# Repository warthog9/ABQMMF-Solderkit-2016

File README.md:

This is the learn to solder badge for the Albuquerque Mini Maker Faire.

License:
	The design is opened based on the Creative Commons CC-BY-SA 4.0
	[https://creativecommons.org/licenses/by-sa/4.0/](https://creativecommons.org/licenses/by-sa/4.0/)

	Copyright on the badge is held by John 'Warthog9' Hawley

	The badges themselves use a silkscreen that has elements that
	have been removed from this repository, they are not required
	for the functionality, and were removed out of respect for the
	various originators of the symbols.

	Rough outline of the balloons was adapted from
	[https://pixabay.com/en/hot-air-balloon-balloon-striped-312574/](https://pixabay.com/en/hot-air-balloon-balloon-striped-312574/)
	which was listed as released into Public Domain when acquired on
	May 27, 2016

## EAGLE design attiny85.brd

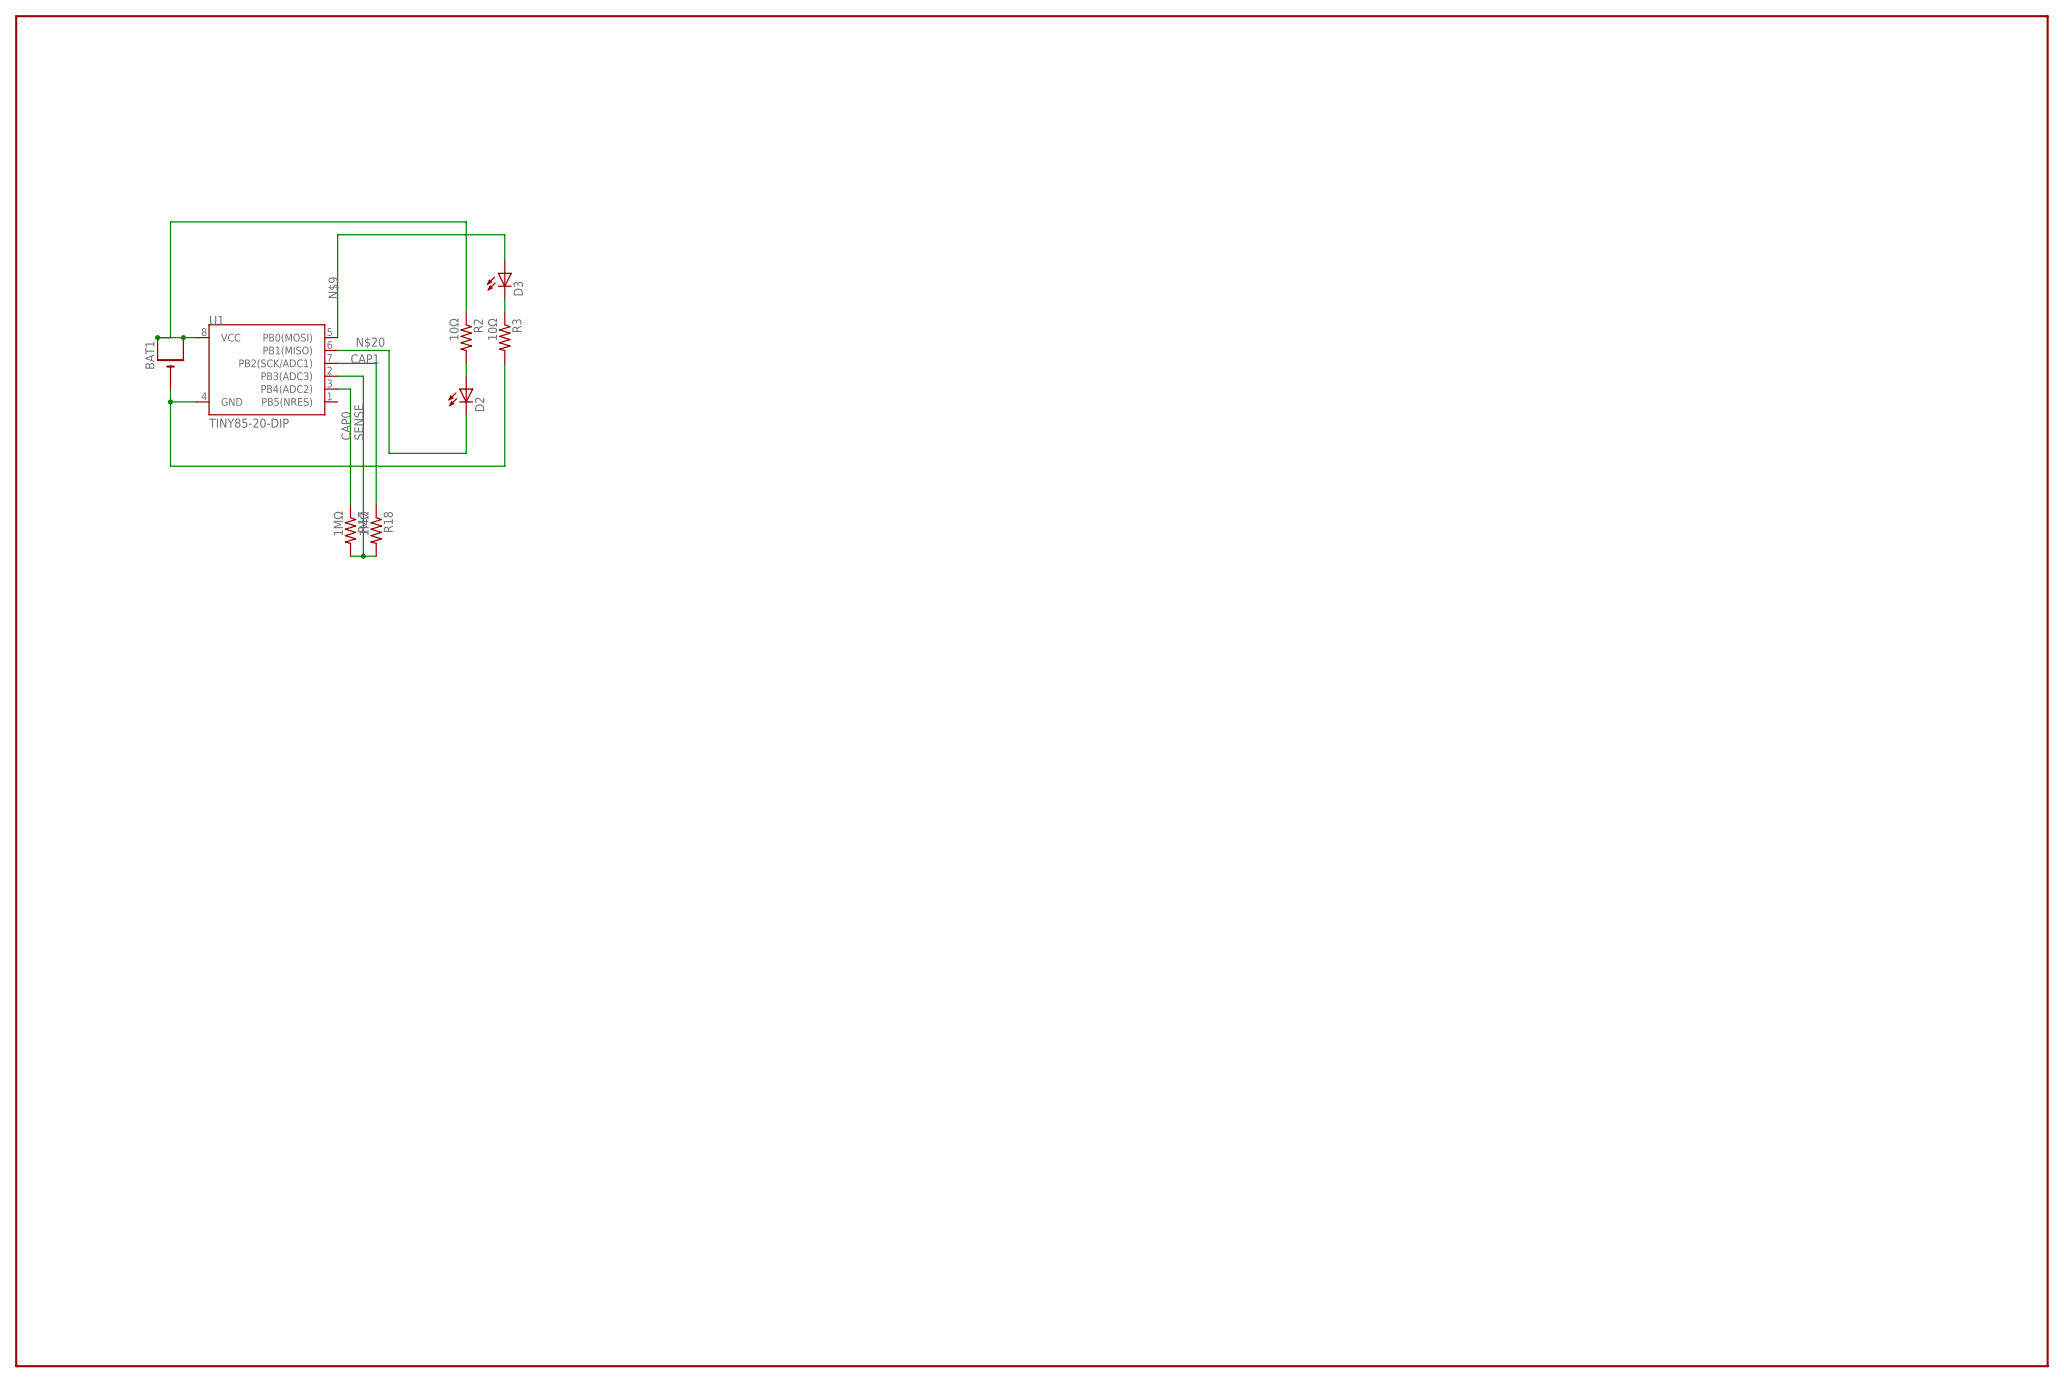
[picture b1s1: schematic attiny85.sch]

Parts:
BAT1: CR2032THM; CR2032-THRU
D2, D3: LED5MM
R2, R3: 10Ω; AXIAL-0.3
R17, R18: 1MΩ; AXIAL-0.3
U1: TINY85-20-DIP; DIP08

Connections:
CAP0: R17.P$1 (1), U1.3 (PB4(ADC2))
CAP1: R18.P$1 (1), U1.7 (PB2(SCK/ADC1))
GND: BAT1.-, R3.P$2 (2), U1.4 (GND)
unnamed: D2.A, R2.P$2 (2)
unnamed: D3.K (C), R3.P$1 (1)
unnamed: D3.A, U1.5 (PB0(MOSI))
unnamed: D2.K (C), U1.6 (PB1(MISO))
SENSE: R17.P$2 (2), R18.P$2 (2), U1.2 (PB3(ADC3))
VCC: BAT1.+1 (+), BAT1.+2 (+1), R2.P$1 (1), U1.8 (VCC)

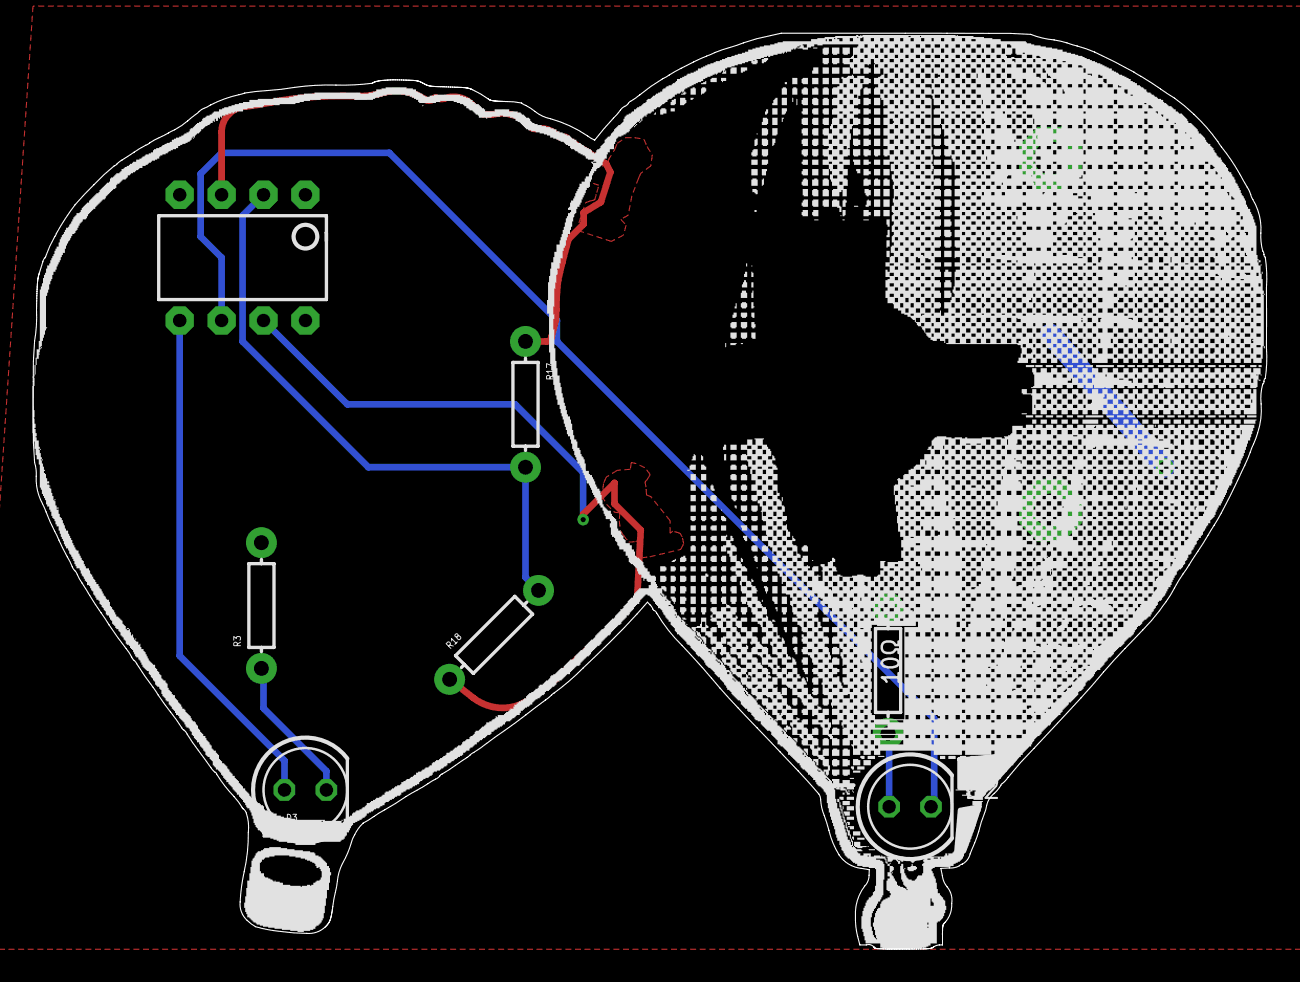
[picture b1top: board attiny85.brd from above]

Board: 2 copper layers, 74.7 x 55.5 mm, 8 parts (1 on the bottom side), 9 nets.

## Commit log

2017-08-11 Minor Cleanups - Silkscreen & Battery Holder
    Battery Holder: Updated so that the rest of the plane isn't also
    exposed on the board
    Silkscreen: mostly minor adjustments, and exposing the right led
    resistor
2017-08-11 Updating resistor values
2017-08-11 Mucking with spacing around the resistor
2017-08-11 More fixing of values
2017-08-11 Adjusting a routing issue
2017-08-11 Updating some wording to fit on board after CAM
2017-08-11 Adding Gerbers
2017-08-11 Adding Arduino Source Code + hex output
    This requires that you have the Arduino board information from
    https://github.com/damellis/attiny
    which is more easily consumed from Sparkfun's site here:
    https://cdn.sparkfun.com/assets/learn_tutorials/1/5/0/attiny-ide-1.6.x.zip
    an entire tutorial on how to set this up can be found here:
    https://learn.sparkfun.com/tutorials/tiny-avr-programmer-hookup-guide
2017-08-11 Adding schematic for the project
2017-08-11 Making the readme a bit more interesting via markdown

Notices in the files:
attiny85.brd:
Licensed CC-BY-SA 4.0 in 2016
parts and their libraries:
SparkFun-DigitalIC: Licensing: Creative Commons ShareAlike 4.0 International - https://creativecommons.org/licenses/by-sa/4.0
